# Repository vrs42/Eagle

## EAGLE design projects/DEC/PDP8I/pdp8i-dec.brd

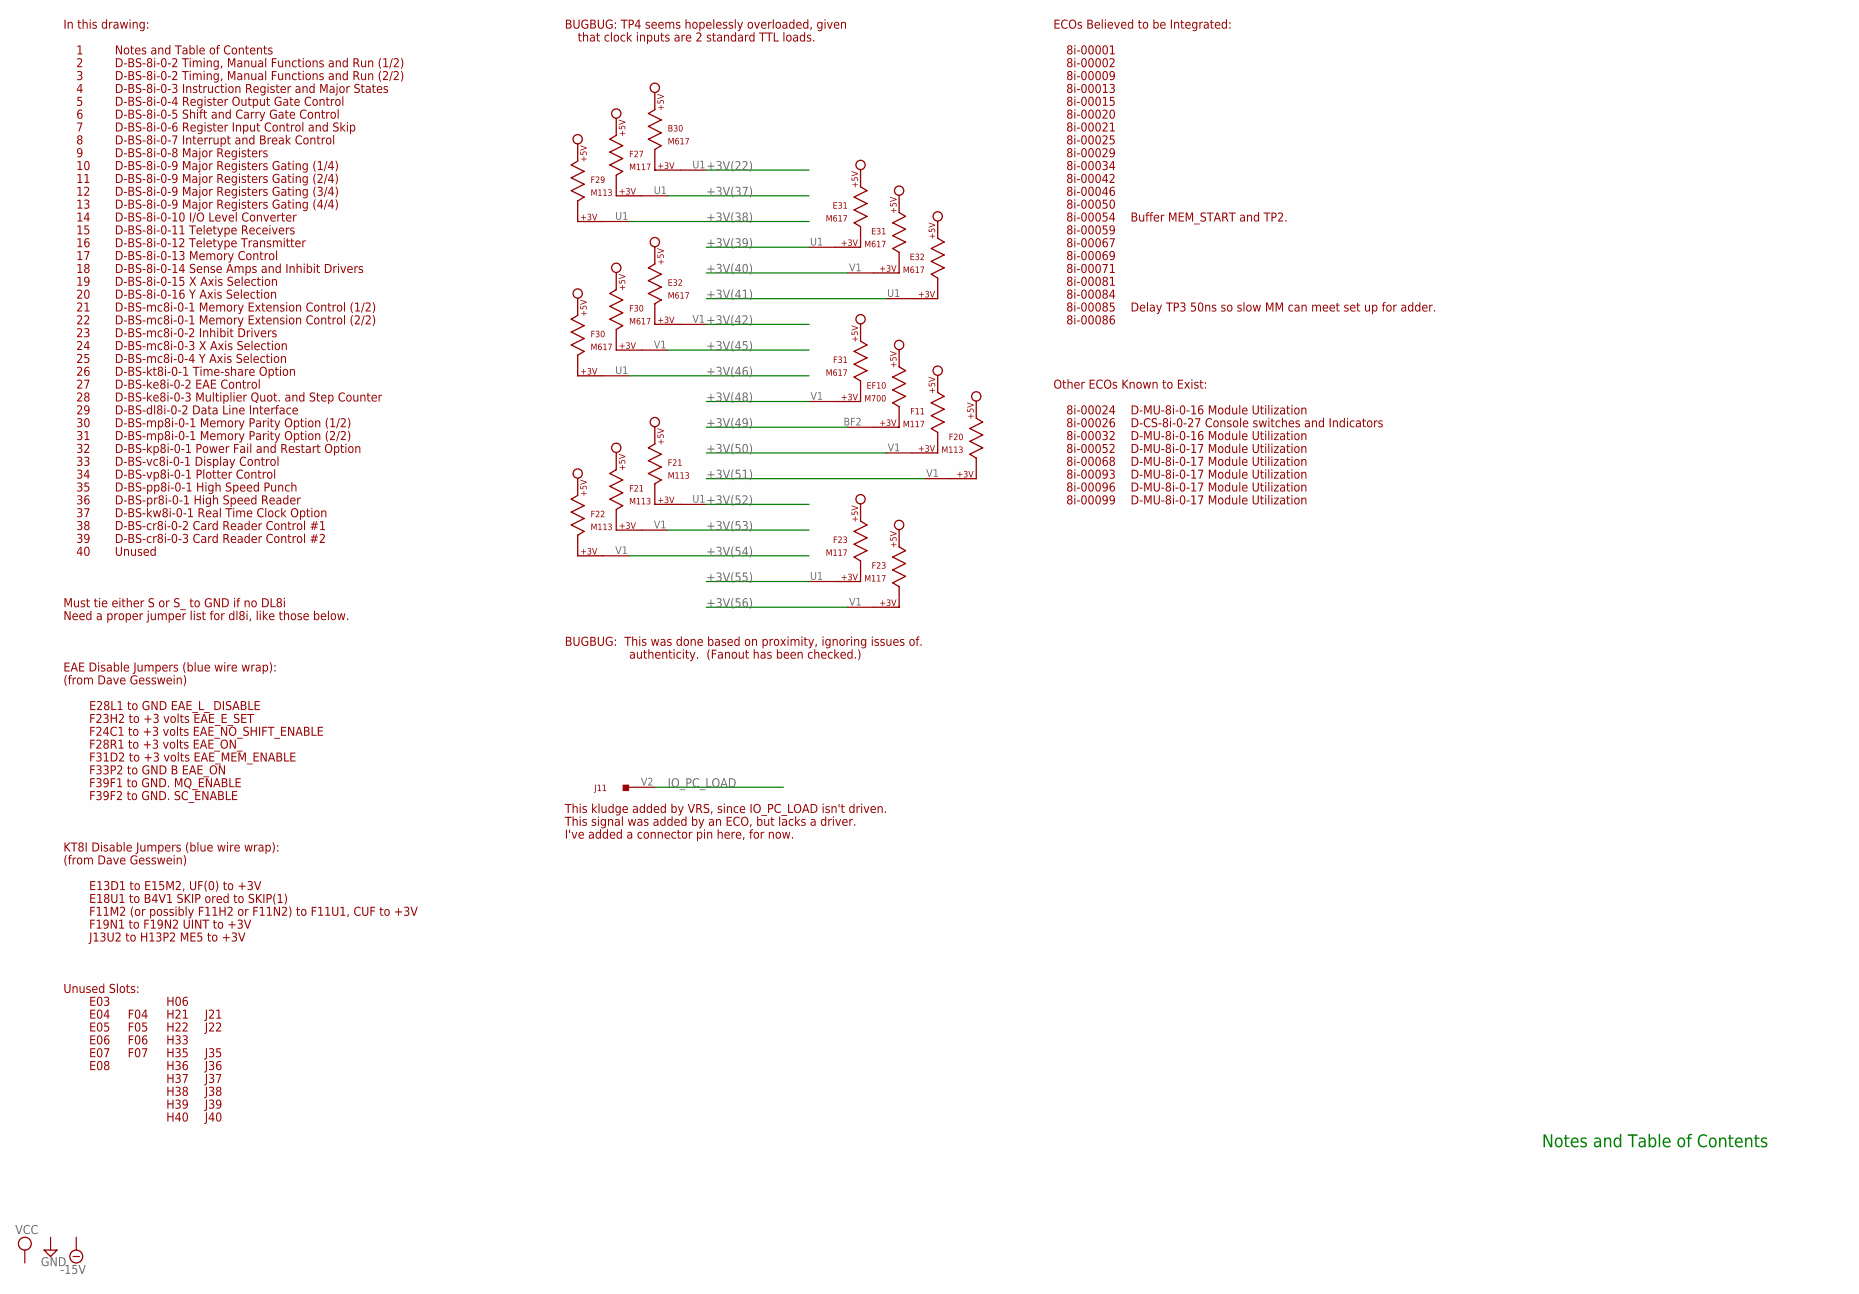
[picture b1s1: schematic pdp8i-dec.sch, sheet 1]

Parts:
B30: M617; H807
E03, E04, E05, E06, E07, E08: EMPTY; H807
E31, E32: M617; H807
EF10: M700; H807-2
F04, F05, F06, F07: EMPTY; H807
F11, F23, F27: M117; H807
F20, F21, F22, F29: M113; H807
F30, F31: M617; H807
H06, H21, H22, H33, H35, H36, H37, H38, H39, H40: EMPTY; H807
J11: W011; H807
J21, J22, J35, J36, J37, J38, J39, J40: EMPTY; H807

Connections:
+3V(22): B30.U1; also elsewhere on the board
+3V(37): F27.U1; also elsewhere on the board
+3V(38): F29.U1; also elsewhere on the board
+3V(39): E31.U1; also elsewhere on the board
+3V(40): E31.V1; also elsewhere on the board
+3V(41): E32.U1; also elsewhere on the board
+3V(42): E32.V1; also elsewhere on the board
+3V(45): F30.V1; also elsewhere on the board
+3V(46): F30.U1; also elsewhere on the board
+3V(48): F31.V1; also elsewhere on the board
+3V(49): EF10.BF2; also elsewhere on the board
+3V(50): F11.V1; also elsewhere on the board
+3V(51): F20.V1; also elsewhere on the board
+3V(52): F21.U1; also elsewhere on the board
+3V(53): F21.V1; also elsewhere on the board
+3V(54): F22.V1; also elsewhere on the board
+3V(55): F23.U1; also elsewhere on the board
+3V(56): F23.V1; also elsewhere on the board
-15V: E03.B2 (-15V), E04.B2 (-15V), E05.B2 (-15V), E06.B2 (-15V), E07.B2 (-15V), E08.B2 (-15V), F04.B2 (-15V), F05.B2 (-15V), F06.B2 (-15V), F07.B2 (-15V), H06.B2 (-15V), H21.B2 (-15V), H22.B2 (-15V), H33.B2 (-15V), H35.B2 (-15V), H36.B2 (-15V), H37.B2 (-15V), H38.B2 (-15V), H39.B2 (-15V), H40.B2 (-15V), J21.B2 (-15V), J22.B2 (-15V), J35.B2 (-15V), J36.B2 (-15V), J37.B2 (-15V), J38.B2 (-15V), J39.B2 (-15V), J40.B2 (-15V); also elsewhere on the board
GND: B30.C2 (GND), B30.T1 (GND), E03.C2 (GND), E04.C2 (GND), E05.C2 (GND), E06.C2 (GND), E07.C2 (GND), E08.C2 (GND), E31.C2 (GND), E31.T1 (GND), E32.C2 (GND), E32.T1 (GND), EF10.AC2 (GND), EF10.BC2 (GND), F04.C2 (GND), F05.C2 (GND), F06.C2 (GND), F07.C2 (GND), F11.C2 (GND), F11.T1 (GND), F20.C2 (GND), F20.T1 (GND), F21.C2 (GND), F21.T1 (GND), F22.C2 (GND), F22.T1 (GND), F23.C2 (GND), F23.T1 (GND), F27.C2 (GND), F27.T1 (GND), F29.C2 (GND), F29.T1 (GND), F30.C2 (GND), F30.T1 (GND), F31.C2 (GND), F31.T1 (GND), H06.C2 (GND), H21.C2 (GND), H22.C2 (GND), H33.C2 (GND), H35.C2 (GND), H36.C2 (GND), H37.C2 (GND), H38.C2 (GND), H39.C2 (GND), H40.C2 (GND), J11.C2 (GND), J11.F2 (GND), J11.J2 (GND), J11.L2 (GND), J11.N2 (GND), J11.R2 (GND), J11.U2 (GND), J21.C2 (GND), J22.C2 (GND), J35.C2 (GND), J36.C2 (GND), J37.C2 (GND), J38.C2 (GND), J39.C2 (GND), J40.C2 (GND); also elsewhere on the board
IO_PC_LOAD: J11.V2; also elsewhere on the board
VCC: B30.A2 (VCC), E03.A2 (VCC), E04.A2 (VCC), E05.A2 (VCC), E06.A2 (VCC), E07.A2 (VCC), E08.A2 (VCC), E31.A2 (VCC), E32.A2 (VCC), EF10.AA2 (VCC), EF10.BA2 (VCC), F04.A2 (VCC), F05.A2 (VCC), F06.A2 (VCC), F07.A2 (VCC), F11.A2 (VCC), F20.A2 (VCC), F21.A2 (VCC), F22.A2 (VCC), F23.A2 (VCC), F27.A2 (VCC), F29.A2 (VCC), F30.A2 (VCC), F31.A2 (VCC), H06.A2 (VCC), H21.A2 (VCC), H22.A2 (VCC), H33.A2 (VCC), H35.A2 (VCC), H36.A2 (VCC), H37.A2 (VCC), H38.A2 (VCC), H39.A2 (VCC), H40.A2 (VCC), J21.A2 (VCC), J22.A2 (VCC), J35.A2 (VCC), J36.A2 (VCC), J37.A2 (VCC), J38.A2 (VCC), J39.A2 (VCC), J40.A2 (VCC); also elsewhere on the board

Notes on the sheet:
BUGBUG: This was done based on proximity, ignoring issues of.
authenticity. (Fanout has been checked.)
EAE Disable Jumpers (blue wire wrap):
F39F1 to GND. MQ_ENABLE
F39F2 to GND. SC_ENABLE
F24C1 to +3 volts EAE_NO_SHIFT_ENABLE
F31D2 to +3 volts EAE_MEM_ENABLE
F33P2 to GND B EAE_ON
F28R1 to +3 volts EAE_ON_
F23H2 to +3 volts EAE_E_SET
E28L1 to GND EAE_L_ DISABLE
Must tie either S or S_ to GND if no DL8i
F11M2 (or possibly F11H2 or F11N2) to F11U1, CUF to +3V
E13D1 to E15M2, UF(0) to +3V
J13U2 to H13P2 ME5 to +3V
F19N1 to F19N2 UINT to +3V
E18U1 to B4V1 SKIP ored to SKIP(1)
KT8I Disable Jumpers (blue wire wrap):
(from Dave Gesswein)
In this drawing:
Unused Slots:
Notes and Table of Contents
ECOs Believed to be Integrated:
8i-00001
8i-00085
Buffer MEM_START and TP2.
Delay TP3 50ns so slow MM can meet set up for adder.
Need a proper jumper list for dl8i, like those below.
This signal was added by an ECO, but lacks a driver.
I've added a connector pin here, for now.
BUGBUG: TP4 seems hopelessly overloaded, given
8i-00013
8i-00054
8i-00002
8i-00015
8i-00020
8i-00021
8i-00025
8i-00050
8i-00042

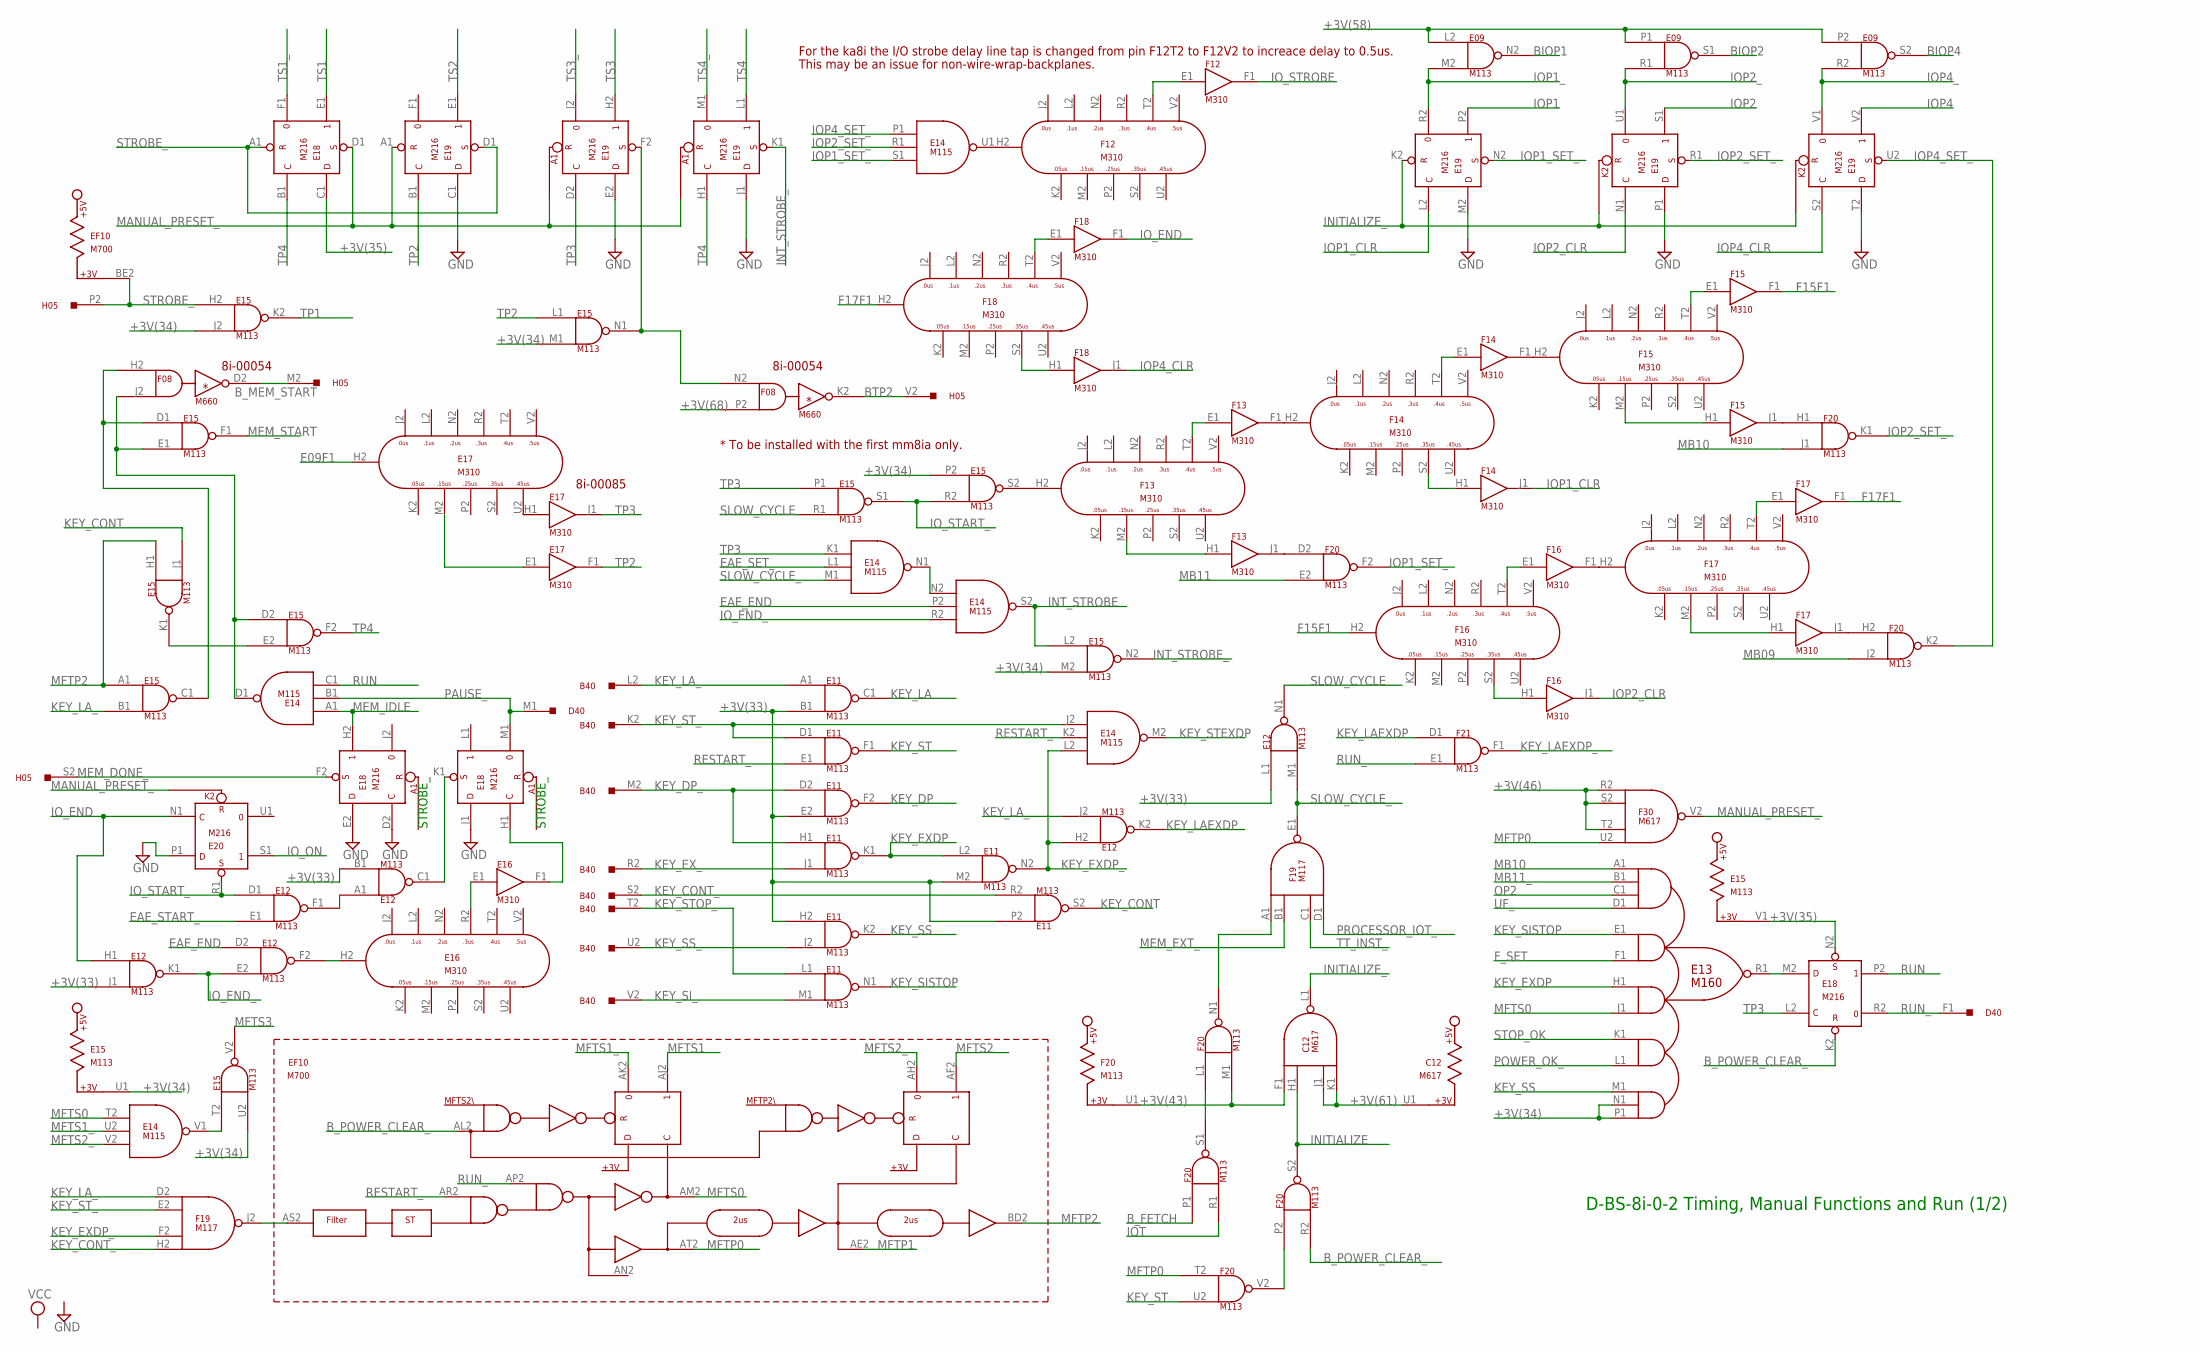
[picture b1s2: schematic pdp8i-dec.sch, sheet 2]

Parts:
B40: W077; H807
C12: M617; H807
D40: M900; H807
E09, E11, E12, E15: M113; H807
E13: M160; H807
E14: M115; H807
E16, E17: M310; H807
E18, E19, E20: M216; H807
EF10: M700; H807-2
F08: M660; H807
F12, F13, F14, F15, F16, F17, F18: M310; H807
F19: M117; H807
F20, F21: M113; H807
F30: M617; H807
H05: W011; H807

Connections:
+3V(33): E11.B1 (IN2), E11.E2 (IN2), E11.H2 (IN1), E11.M2 (IN2), E11.P2 (IN1), E12.B1 (IN2), E12.J1 (IN2), E12.L1 (IN1); also elsewhere on the board
+3V(34): E13.N1 (IN5B), E13.P1 (IN5C), E15.J2 (IN2), E15.M1 (IN2), E15.M2 (IN2), E15.P2 (IN1), E15.U1, E15.U2 (IN2)
+3V(35): E15.V1, E18.C1 (D), E18.N2 (S); also elsewhere on the board
+3V(43): C12.F1 (IN1), F20.M1 (IN2), F20.U1; also elsewhere on the board
+3V(46): F30.R2 (IN1), F30.S2 (IN2), F30.T2 (IN3); also elsewhere on the board
+3V(58): E09.L2 (IN1), E09.P1 (IN1), E09.P2 (IN1); also elsewhere on the board
+3V(61): C12.J1 (IN3), C12.K1 (IN4), C12.U1; also elsewhere on the board
+3V(68): F08.P2 (IN2); also elsewhere on the board
BIOP1: E09.N2 (OUT); also elsewhere on the board
BIOP2: E09.S1 (OUT); also elsewhere on the board
BIOP4: E09.S2 (OUT); also elsewhere on the board
BTP2: F08.K2 (OUT), H05.V2
B_FETCH: F20.P1 (IN1); also elsewhere on the board
B_MEM_START: F08.D2 (OUT), H05.M2
B_POWER_CLEAR_: E18.K2 (R), EF10.AL2 (CL2), F20.R2 (IN2); also elsewhere on the board
E09F1: E17.H2; also elsewhere on the board
EAE_END: E12.D2 (IN1), E14.P2 (IN2); also elsewhere on the board
EAE_SET_: E14.L1 (IN2); also elsewhere on the board
EAE_START_: E12.E1 (IN2); also elsewhere on the board
F15F1: F15.F1 (OUT), F16.H2
F17F1: F17.F1 (OUT), F18.H2
F_SET: E13.F1 (IN2B); also elsewhere on the board
GND: C12.C2 (GND), C12.T1 (GND), E09.C2 (GND), E09.T1 (GND), E11.C2 (GND), E11.T1 (GND), E12.C2 (GND), E12.T1 (GND), E13.C2 (GND), E13.T1 (GND), E14.C2 (GND), E14.T1 (GND), E15.C2 (GND), E15.T1 (GND), E16.C2 (GND), E16.T1 (GND), E17.C2 (GND), E17.T1 (GND), E18.C2 (GND), E18.D2 (C), E18.E2 (D), E18.J1 (D), E18.T1 (GND), E19.C1 (D), E19.C2 (GND), E19.E2 (D), E19.J1 (D), E19.M2 (D), E19.P1 (D), E19.T1 (GND), E19.T2 (D), E20.C2 (GND), E20.P1 (D), E20.T1 (GND), EF10.AC2 (GND), EF10.BC2 (GND), F08.C2 (GND), F12.C2 (GND), F12.T1 (GND), F13.C2 (GND), F13.T1 (GND), F14.C2 (GND), F14.T1 (GND), F15.C2 (GND), F15.T1 (GND), F16.C2 (GND), F16.T1 (GND), F17.C2 (GND), F17.T1 (GND), F18.C2 (GND), F18.T1 (GND), F19.C2 (GND), F19.T1 (GND), F20.C2 (GND), F20.T1 (GND), F21.C2 (GND), F21.T1 (GND), F30.C2 (GND), F30.T1 (GND), H05.C2 (GND), H05.F2 (GND), H05.J2 (GND), H05.L2 (GND), H05.N2 (GND), H05.R2 (GND), H05.U2 (GND); also elsewhere on the board
INITIALIZE: C12.H1 (IN2), F20.S2 (OUT); also elsewhere on the board
INITIALIZE_: C12.L1 (OUT), E19.K2 (R); also elsewhere on the board
INT_STROBE: E14.S2 (OUT), E15.L2 (IN1); also elsewhere on the board
INT_STROBE_: E15.N2 (OUT), E19.K1 (S); also elsewhere on the board
IOP1: E19.P2 (1); also elsewhere on the board
IOP1_: E09.M2 (IN2), E19.R2 (0); also elsewhere on the board
IOP1_CLR: E19.L2 (C), F14.J1 (OUT)
IOP1_SET_: E14.S1 (IN3), E19.N2 (S), F20.F2 (OUT)
IOP2: E19.S1 (1); also elsewhere on the board
IOP2_: E09.R1 (IN2), E19.U1 (0); also elsewhere on the board
IOP2_CLR: E19.N1 (C), F16.J1 (OUT)
IOP2_SET_: E14.R1 (IN2), E19.R1 (S), F20.K1 (OUT)
IOP4: E19.V2 (1); also elsewhere on the board
IOP4_: E09.R2 (IN2), E19.V1 (0); also elsewhere on the board
IOP4_CLR: E19.S2 (C), F18.J1 (OUT)
IOP4_SET_: E14.P1 (IN1), E19.U2 (S), F20.K2 (OUT)
IOT: F20.R1 (IN2); also elsewhere on the board
IO_END: E12.H1 (IN1), E20.N1 (C), F18.F1 (OUT)
IO_END_: E12.E2 (IN2), E12.K1 (OUT), E14.R2 (IN3)
IO_ON: E20.S1 (1); also elsewhere on the board
IO_START_: E12.D1 (IN1), E15.R2 (IN2), E15.S1 (OUT), E20.R1 (S)
IO_STROBE: F12.F1 (OUT); also elsewhere on the board
KEY_CONT: E11.S2 (OUT), E15.J1 (IN2)
KEY_CONT_: B40.S2, E11.R2 (IN2), F19.H2 (IN4)
KEY_DP: E11.F2 (OUT); also elsewhere on the board
KEY_DP_: B40.M2, E11.D2 (IN1), E11.H1 (IN1)
KEY_EXDP: E11.K1 (OUT), E11.L2 (IN1), E13.H1 (IN3A); also elsewhere on the board
KEY_EXDP_: E11.N2 (OUT), E12.H2 (IN1), E14.L2 (IN3), F19.F2 (IN3)
KEY_EX_: B40.R2, E11.J1 (IN2)
KEY_LA: E11.C1 (OUT); also elsewhere on the board
KEY_LAEXDP: E12.K2 (OUT), F21.D1 (IN1); also elsewhere on the board
KEY_LAEXDP_: F21.F1 (OUT); also elsewhere on the board
KEY_LA_: B40.L2, E11.A1 (IN1), E12.J2 (IN2), E15.B1 (IN2), F19.D2 (IN1)
KEY_SISTOP: E11.N1 (OUT), E13.E1 (IN2A)
KEY_SI_: B40.V2, E11.M1 (IN2)
KEY_SS: E11.K2 (OUT), E13.M1 (IN5A)
KEY_SS_: B40.U2, E11.J2 (IN2)
KEY_ST: E11.F1 (OUT), F20.U2 (IN2); also elsewhere on the board
KEY_STEXDP: E14.M2 (OUT); also elsewhere on the board
KEY_STOP_: B40.T2, E11.L1 (IN1)
KEY_ST_: B40.K2, E11.D1 (IN1), E14.J2 (IN1), F19.E2 (IN2)
MANUAL_PRESET_: E18.D1 (S), E19.A1 (R), F30.V2 (OUT); also elsewhere on the board
MB09: F20.J2 (IN2); also elsewhere on the board
MB10: E13.A1 (IN1A), F20.J1 (IN2); also elsewhere on the board
MB11: F20.E2 (IN2); also elsewhere on the board
MB11_: E13.B1 (IN1B); also elsewhere on the board
MEM_DONE_: E18.F2 (S), H05.S2; also elsewhere on the board
MEM_EXT_: F19.B1 (IN2); also elsewhere on the board
MEM_IDLE: E14.A1 (IN1), E18.H2 (1)
MEM_START: E15.F1 (OUT); also elsewhere on the board
MFTP0: EF10.AT2 (CT2), F20.T2 (IN1), F30.U2 (IN4)
MFTP1: EF10.AE2 (CE2); also elsewhere on the board
MFTP2: E15.A1 (IN1), E15.H1 (IN1), EF10.BD2 (DD2); also elsewhere on the board
MFTS0: E13.J1 (IN3B), E14.T2 (IN1), EF10.AM2 (CM2); also elsewhere on the board
MFTS1: EF10.AJ2 (CJ2); also elsewhere on the board
MFTS1_: E14.U2 (IN2), EF10.AK2 (CK2)
MFTS2: EF10.AF2 (CF2); also elsewhere on the board
MFTS2_: E14.V2 (IN3), EF10.AH2 (CH2); also elsewhere on the board
MFTS3: E15.V2 (OUT); also elsewhere on the board
unnamed: EF10.AS2 (CS2), F19.J2 (OUT)
unnamed: F20.P2 (IN1), F20.V2 (OUT)
unnamed: F20.L1 (IN1), F20.S1 (OUT)
unnamed: E13.R1 (OUT), E18.M2 (D)
unnamed: F19.A1 (IN1), F20.N1 (OUT)
unnamed: E14.V1 (OUT), E15.T2 (IN1)
unnamed: E16.E1 (IN), E16.R2
unnamed: E12.A1 (IN1), E12.F1 (OUT)
unnamed: E12.C1 (OUT), E18.K1 (S)
unnamed: E12.F2 (OUT), E16.H2
unnamed: E16.F1 (OUT), E18.H1 (C)
unnamed: E14.D1 (OUT), E15.D2 (IN1), E15.E1 (IN2), F08.J2 (IN2)
unnamed: E15.C1 (OUT), E15.D1 (IN1), F08.H2 (IN1)
unnamed: E15.E2 (IN2), E15.K1 (OUT)
unnamed: E17.E1 (IN), E17.M2
unnamed: E15.N1 (OUT), E19.F2 (S), F08.N2 (IN1)
unnamed: E14.N1 (OUT), E14.N2 (IN1)
unnamed: E15.S2 (OUT), F13.H2
unnamed: F13.H1 (IN), F13.M2
unnamed: F13.E1 (IN), F13.T2
unnamed: F13.F1 (OUT), F14.H2
unnamed: F14.H1 (IN), F14.S2
unnamed: F14.E1 (IN), F14.T2
unnamed: F14.F1 (OUT), F15.H2
unnamed: F13.J1 (OUT), F20.D2 (IN1)
unnamed: F15.H1 (IN), F15.M2
unnamed: F15.E1 (IN), F15.T2
unnamed: F15.J1 (OUT), F20.H1 (IN1)
unnamed: F16.H1 (IN), F16.S2
unnamed: F16.E1 (IN), F16.T2
unnamed: F16.F1 (OUT), F17.H2
unnamed: F17.H1 (IN), F17.M2
unnamed: F17.E1 (IN), F17.T2
unnamed: F17.J1 (OUT), F20.H2 (IN1)
unnamed: E14.U1 (OUT), F12.H2
unnamed: F12.E1 (IN), F12.T2
unnamed: F18.H1 (IN), F18.S2
unnamed: F18.E1 (IN), F18.T2
unnamed: E17.H1 (IN), E17.U2
OP2: E13.C1 (IN1C); also elsewhere on the board
PAUSE_: D40.M1, E14.B1 (IN2), E18.M1 (0)
POWER_OK_: E13.L1 (IN4B); also elsewhere on the board
PROCESSOR_IOT_: F19.D1 (IN4); also elsewhere on the board
RESTART_: E11.E1 (IN2), E14.K2 (IN2), EF10.AR2 (CR2); also elsewhere on the board
RUN: E14.C1 (IN3), E18.P2 (1); also elsewhere on the board
RUN_: D40.F1, E18.R2 (0), EF10.AP2 (CP2), F21.E1 (IN2); also elsewhere on the board
SLOW_CYCLE: E12.N1 (OUT), E15.R1 (IN2)
SLOW_CYCLE_: E12.M1 (IN2), E14.M1 (IN3), F19.E1 (OUT)
STOP_OK: E13.K1 (IN4A); also elsewhere on the board
STROBE_: E15.H2 (IN1), E18.A1 (R), E19.D1 (S), EF10.BE2, H05.P2; also elsewhere on the board
TP1: E15.K2 (OUT); also elsewhere on the board
TP2: E15.L1 (IN1), E17.F1 (OUT), E19.B1 (C); also elsewhere on the board
TP3: E14.K1 (IN1), E15.P1 (IN1), E17.J1 (OUT), E18.L2 (C), E19.D2 (C); also elsewhere on the board
TP4: E15.F2 (OUT), E18.B1 (C), E19.H1 (C); also elsewhere on the board
TS1: E18.E1 (1); also elsewhere on the board
TS1_: E18.F1 (0); also elsewhere on the board
TS2: E19.E1 (1); also elsewhere on the board
TS3: E19.H2 (1); also elsewhere on the board
TS3_: E19.J2 (0); also elsewhere on the board
TS4: E19.L1 (1); also elsewhere on the board
TS4_: E19.M1 (0); also elsewhere on the board
TT_INST_: F19.C1 (IN3); also elsewhere on the board
UF_: E13.D1 (IN1D); also elsewhere on the board
VCC: C12.A2 (VCC), E09.A2 (VCC), E11.A2 (VCC), E12.A2 (VCC), E13.A2 (VCC), E14.A2 (VCC), E15.A2 (VCC), E16.A2 (VCC), E17.A2 (VCC), E18.A2 (VCC), E19.A2 (VCC), E20.A2 (VCC), EF10.AA2 (VCC), EF10.BA2 (VCC), F08.A2 (VCC), F12.A2 (VCC), F13.A2 (VCC), F14.A2 (VCC), F15.A2 (VCC), F16.A2 (VCC), F17.A2 (VCC), F18.A2 (VCC), F19.A2 (VCC), F20.A2 (VCC), F21.A2 (VCC), F30.A2 (VCC); also elsewhere on the board

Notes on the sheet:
D-BS-8i-0-2 Timing, Manual Functions and Run (1/2)
STROBE_
8i-00085
8i-00054
For the ka8i the I/O strobe delay line tap is changed from pin F12T2 to F12V2 to increace delay to 0.5us.
* To be installed with the first mm8ia only.
This may be an issue for non-wire-wrap-backplanes.

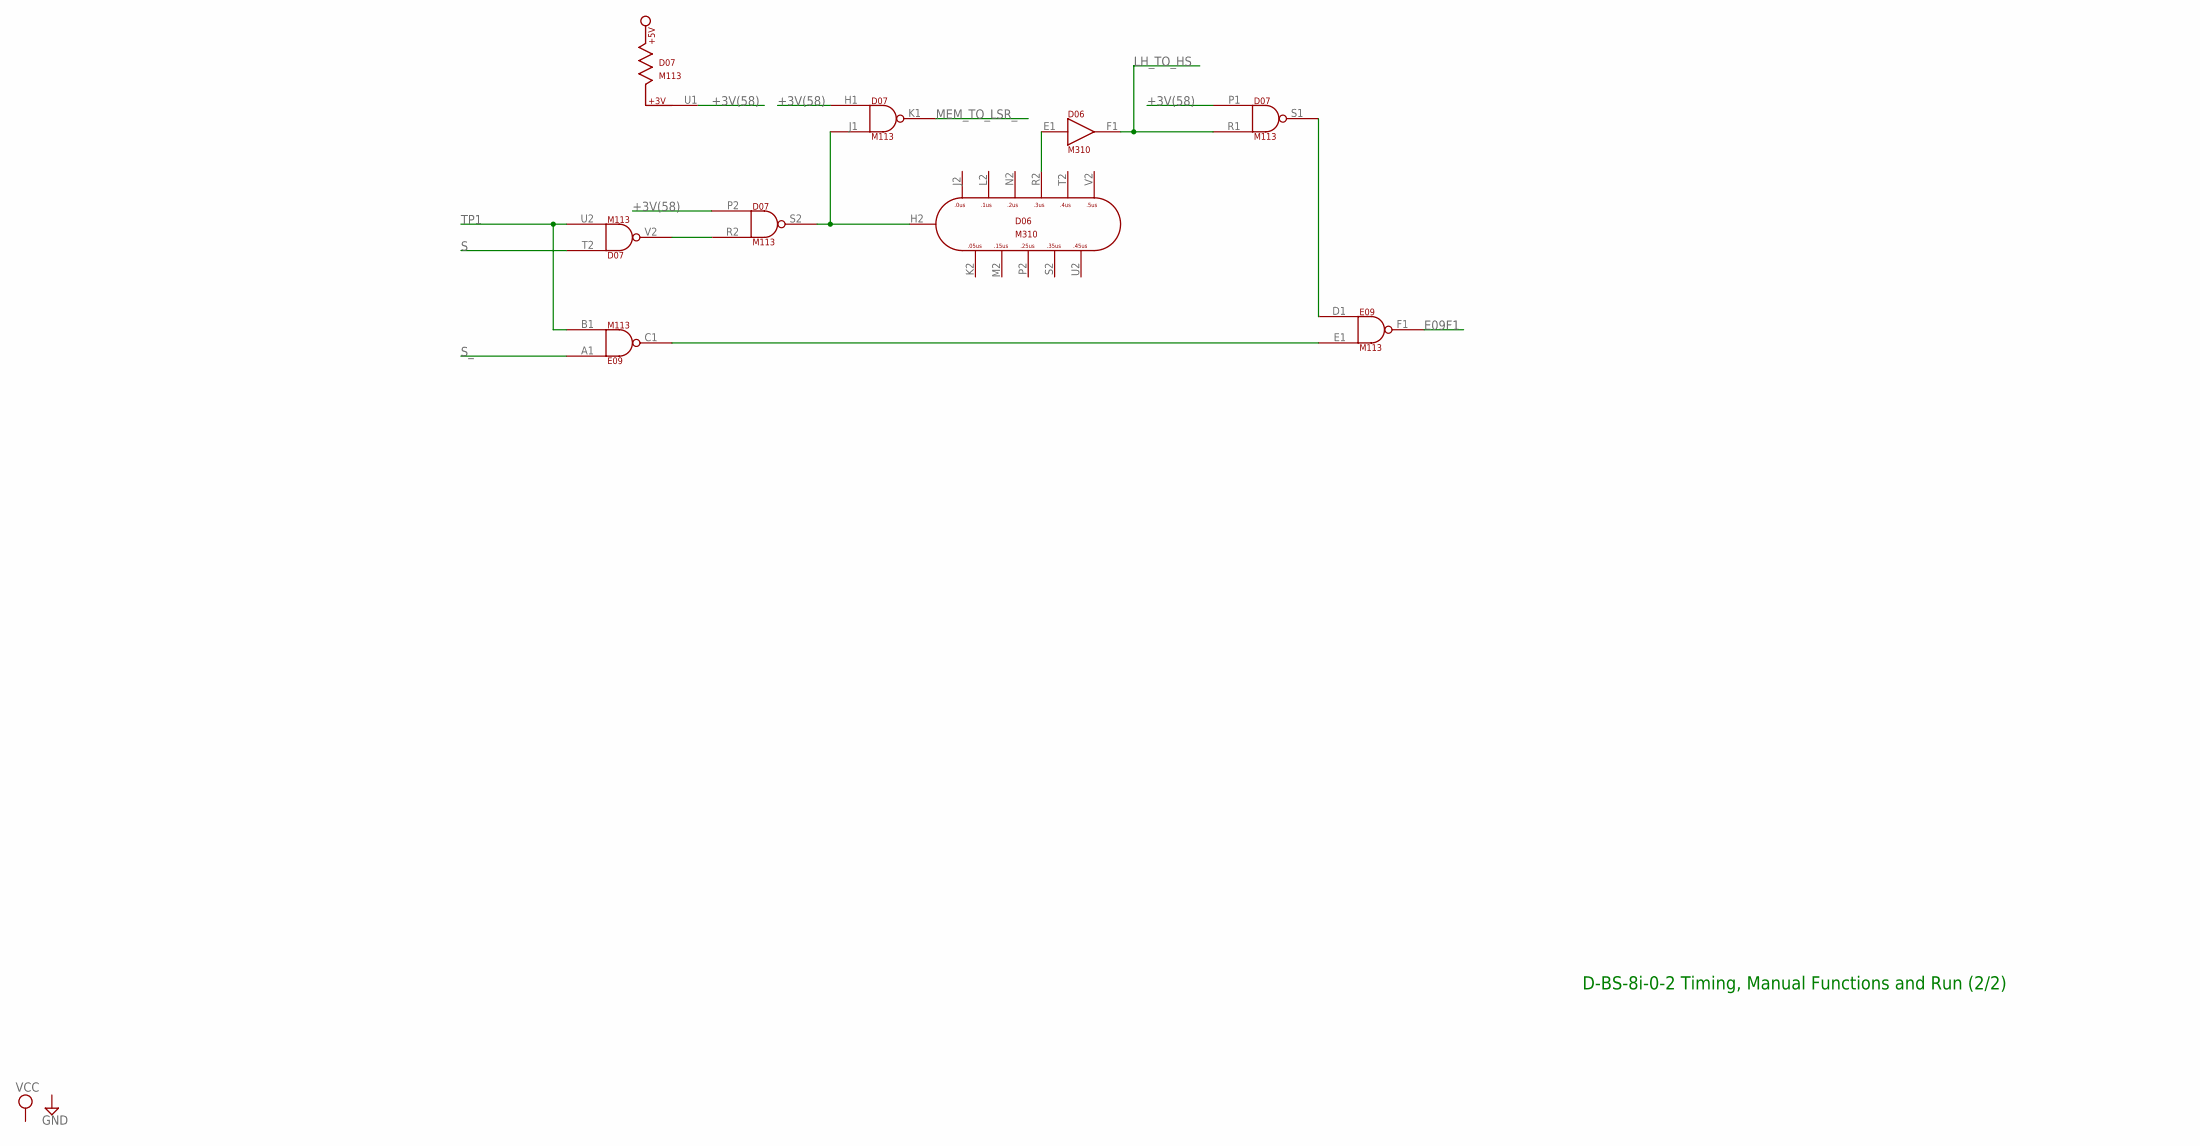
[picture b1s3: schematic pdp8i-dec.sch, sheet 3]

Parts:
D06: M310; H807
D07: M113; H807
E09: M113; H807

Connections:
+3V(58): D07.H1 (IN1), D07.P1 (IN1), D07.P2 (IN1), D07.U1; also elsewhere on the board
E09F1: E09.F1 (OUT); also elsewhere on the board
GND: D06.C2 (GND), D06.T1 (GND), D07.C2 (GND), D07.T1 (GND), E09.C2 (GND), E09.T1 (GND); also elsewhere on the board
LH_TO_HS: D06.F1 (OUT), D07.R1 (IN2); also elsewhere on the board
MEM_TO_LSR_: D07.K1 (OUT); also elsewhere on the board
unnamed: E09.C1 (OUT), E09.E1 (IN2)
unnamed: D07.R2 (IN2), D07.V2 (OUT)
unnamed: D06.H2, D07.J1 (IN2), D07.S2 (OUT)
unnamed: D06.E1 (IN), D06.R2
unnamed: D07.S1 (OUT), E09.D1 (IN1)
S: D07.T2 (IN1); also elsewhere on the board
S_: E09.A1 (IN1); also elsewhere on the board
TP1: D07.U2 (IN2), E09.B1 (IN2); also elsewhere on the board
VCC: D06.A2 (VCC), D07.A2 (VCC), E09.A2 (VCC); also elsewhere on the board

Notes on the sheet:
D-BS-8i-0-2 Timing, Manual Functions and Run (2/2)

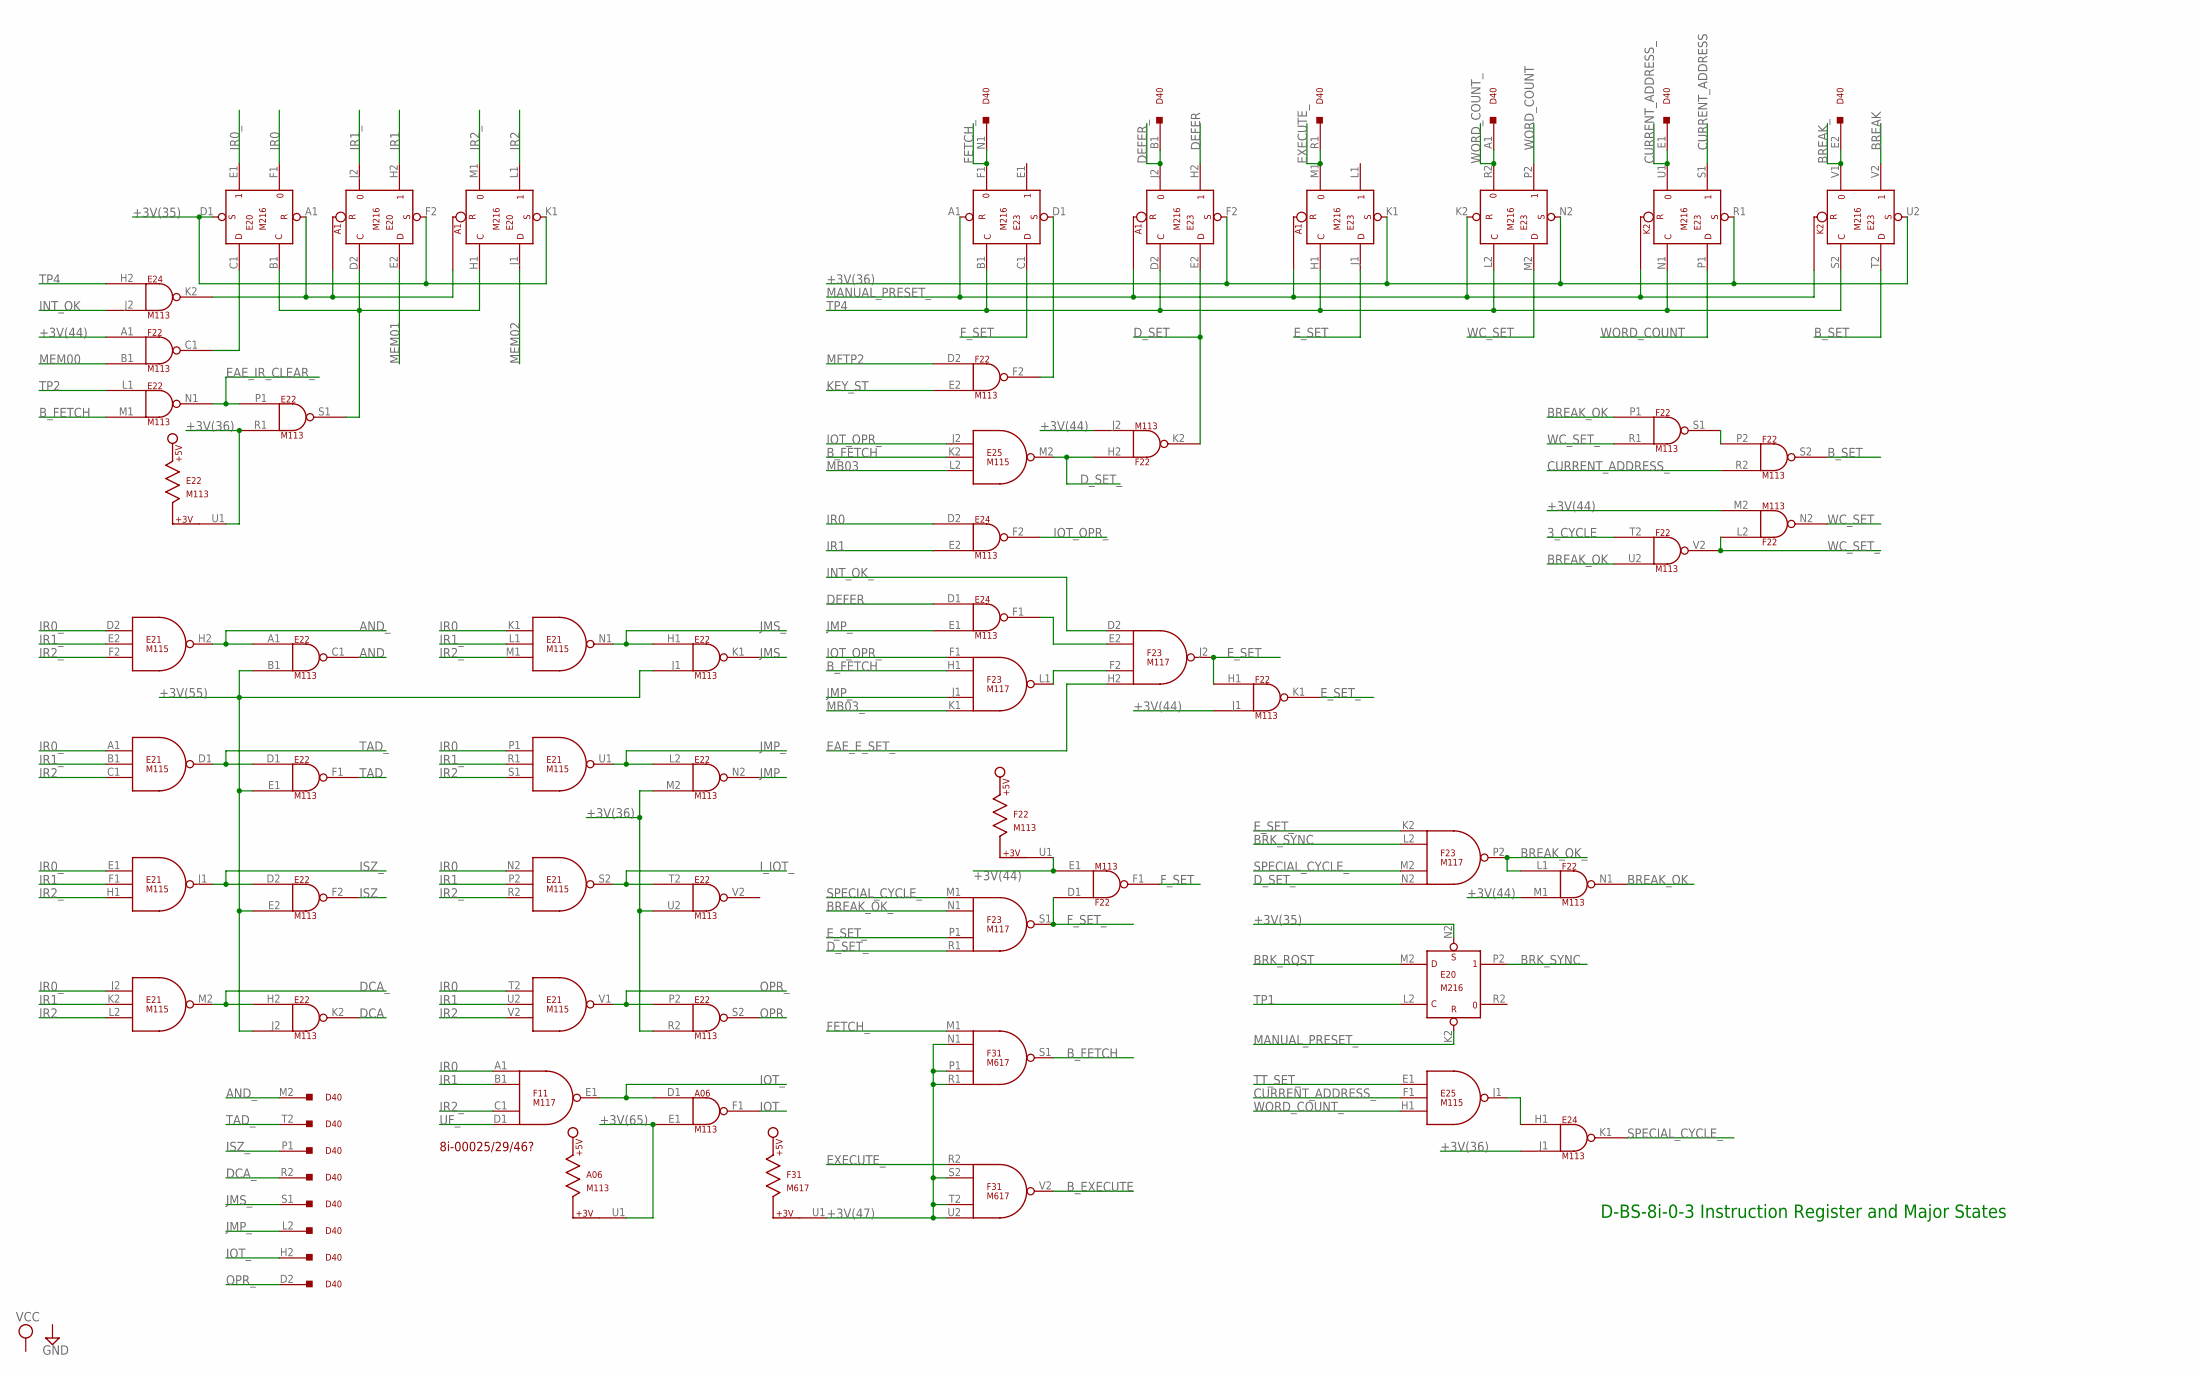
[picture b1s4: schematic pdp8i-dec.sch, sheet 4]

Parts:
A06: M113; H807
D40: M900; H807
E20, E23: M216; H807
E21, E25: M115; H807
E22, E24: M113; H807
F11, F23: M117; H807
F22: M113; H807
F31: M617; H807

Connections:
3_CYCLE: F22.T2 (IN1); also elsewhere on the board
+3V(35): E20.D1 (S), E20.F2 (S), E20.K1 (S), E20.N2 (S); also elsewhere on the board
+3V(36): E22.M2 (IN2), E22.R1 (IN2), E22.R2 (IN2), E22.U1, E22.U2 (IN2), E23.F2 (S), E23.K1 (S), E23.N2 (S), E23.R1 (S), E23.U2 (S), E24.J1 (IN2); also elsewhere on the board
+3V(44): F22.A1 (IN1), F22.E1 (IN2), F22.J1 (IN2), F22.J2 (IN2), F22.M1 (IN2), F22.M2 (IN2), F22.U1; also elsewhere on the board
+3V(47): F31.N1 (IN2), F31.P1 (IN3), F31.R1 (IN4), F31.S2 (IN2), F31.T2 (IN3), F31.U1, F31.U2 (IN4); also elsewhere on the board
+3V(55): E22.B1 (IN2), E22.E1 (IN2), E22.E2 (IN2), E22.J1 (IN2), E22.J2 (IN2); also elsewhere on the board
+3V(65): A06.E1 (IN2), A06.U1; also elsewhere on the board
AND: E22.C1 (OUT); also elsewhere on the board
AND_: D40.M2, E21.H2 (OUT), E22.A1 (IN1); also elsewhere on the board
BREAK: E23.V2 (1); also elsewhere on the board
BREAK_: D40.E2, E23.V1 (0); also elsewhere on the board
BREAK_OK: F22.N1 (OUT), F22.P1 (IN1), F22.U2 (IN2); also elsewhere on the board
BREAK_OK_: F22.L1 (IN1), F23.N1 (IN2), F23.P2 (OUT); also elsewhere on the board
BRK_RQST: E20.M2 (D); also elsewhere on the board
BRK_SYNC: E20.P2 (1), F23.L2 (IN2)
B_EXECUTE: F31.V2 (OUT); also elsewhere on the board
B_FETCH: E22.M1 (IN2), E25.K2 (IN2), F23.H1 (IN2), F31.S1 (OUT); also elsewhere on the board
B_SET: E23.T2 (D), F22.S2 (OUT); also elsewhere on the board
CURRENT_ADDRESS: E23.S1 (1); also elsewhere on the board
CURRENT_ADDRESS_: D40.E1, E23.U1 (0), E25.F1 (IN2), F22.R2 (IN2)
DCA: E22.K2 (OUT); also elsewhere on the board
DCA_: D40.R2, E21.M2 (OUT), E22.H2 (IN1); also elsewhere on the board
DEFER: E23.H2 (1), E24.D1 (IN1); also elsewhere on the board
DEFER_: D40.B1, E23.J2 (0)
D_SET: E23.E2 (D), F22.K2 (OUT)
D_SET_: E25.M2 (OUT), F22.H2 (IN1), F23.N2 (IN4), F23.R1 (IN4); also elsewhere on the board
EAE_E_SET_: F23.H2 (IN4); also elsewhere on the board
EAE_IR_CLEAR_: E22.N1 (OUT), E22.P1 (IN1); also elsewhere on the board
EXECUTE_: D40.R1, E23.M1 (0), F31.R2 (IN1)
E_SET: E23.J1 (D), F22.H1 (IN1), F23.J2 (OUT)
E_SET_: F22.K1 (OUT), F23.K2 (IN1), F23.P1 (IN3); also elsewhere on the board
FETCH_: D40.N1, E23.F1 (0), F31.M1 (IN1); also elsewhere on the board
F_SET: E23.C1 (D), F22.F1 (OUT); also elsewhere on the board
F_SET_: F22.D1 (IN1), F23.S1 (OUT); also elsewhere on the board
GND: A06.C2 (GND), A06.T1 (GND), E20.C2 (GND), E20.T1 (GND), E21.C2 (GND), E21.T1 (GND), E22.C2 (GND), E22.T1 (GND), E23.C2 (GND), E23.T1 (GND), E24.C2 (GND), E24.T1 (GND), E25.C2 (GND), E25.T1 (GND), F11.C2 (GND), F11.T1 (GND), F22.C2 (GND), F22.T1 (GND), F23.C2 (GND), F23.T1 (GND), F31.C2 (GND), F31.T1 (GND); also elsewhere on the board
INT_OK: E24.J2 (IN2); also elsewhere on the board
INT_OK_: F23.D2 (IN1); also elsewhere on the board
IOT: A06.F1 (OUT); also elsewhere on the board
IOT_: A06.D1 (IN1), D40.H2, F11.E1 (OUT)
IOT_OPR_: E24.F2 (OUT), E25.J2 (IN1), F23.F1 (IN1)
IR0: E20.F1 (0), E21.K1 (IN1), E21.N2 (IN1), E21.P1 (IN1), E21.T2 (IN1), E24.D2 (IN1), F11.A1 (IN1)
IR0_: E20.E1 (1), E21.A1 (IN1), E21.D2 (IN1), E21.E1 (IN1), E21.J2 (IN1)
IR1: E20.H2 (1), E21.F1 (IN2), E21.K2 (IN2), E21.P2 (IN2), E21.U2 (IN2), E24.E2 (IN2), F11.B1 (IN2)
IR1_: E20.J2 (0), E21.B1 (IN2), E21.E2 (IN2), E21.L1 (IN2), E21.R1 (IN2)
IR2: E20.L1 (1), E21.C1 (IN3), E21.L2 (IN3), E21.S1 (IN3), E21.V2 (IN3)
IR2_: E20.M1 (0), E21.F2 (IN3), E21.H1 (IN3), E21.M1 (IN3), E21.R2 (IN3), F11.C1 (IN3)
ISZ: E22.F2 (OUT); also elsewhere on the board
ISZ_: D40.P1, E21.J1 (OUT), E22.D2 (IN1)
I_IOT_: E21.S2 (OUT), E22.T2 (IN1); also elsewhere on the board
JMP: E22.N2 (OUT); also elsewhere on the board
JMP_: D40.L2, E21.U1 (OUT), E22.L2 (IN1), E24.E1 (IN2), F23.J1 (IN3); also elsewhere on the board
JMS: E22.K1 (OUT); also elsewhere on the board
JMS_: D40.S1, E21.N1 (OUT), E22.H1 (IN1); also elsewhere on the board
KEY_ST: F22.E2 (IN2); also elsewhere on the board
MANUAL_PRESET_: E20.K2 (R), E23.A1 (R), E23.K2 (R); also elsewhere on the board
MB03: E25.L2 (IN3); also elsewhere on the board
MB03_: F23.K1 (IN4); also elsewhere on the board
MEM00: F22.B1 (IN2); also elsewhere on the board
MEM01: E20.E2 (D); also elsewhere on the board
MEM02: E20.J1 (D); also elsewhere on the board
MFTP2: F22.D2 (IN1); also elsewhere on the board
unnamed: E20.A1 (R), E24.K2 (OUT)
unnamed: E20.C1 (D), F22.C1 (OUT)
unnamed: E20.B1 (C), E20.D2 (C), E20.H1 (C), E22.S1 (OUT)
unnamed: E23.D1 (S), F22.F2 (OUT)
unnamed: E24.F1 (OUT), F23.E2 (IN2)
unnamed: F23.F2 (IN3), F23.L1 (OUT)
unnamed: F22.P2 (IN1), F22.S1 (OUT)
unnamed: E24.H1 (IN1), E25.J1 (OUT)
OPR: E22.S2 (OUT); also elsewhere on the board
OPR_: D40.D2, E21.V1 (OUT), E22.P2 (IN1)
SPECIAL_CYCLE_: E24.K1 (OUT), F23.M1 (IN1), F23.M2 (IN3)
TAD: E22.F1 (OUT); also elsewhere on the board
TAD_: D40.T2, E21.D1 (OUT), E22.D1 (IN1); also elsewhere on the board
TP1: E20.L2 (C); also elsewhere on the board
TP2: E22.L1 (IN1); also elsewhere on the board
TP4: E23.B1 (C), E23.D2 (C), E23.H1 (C), E23.L2 (C), E23.N1 (C), E23.S2 (C), E24.H2 (IN1); also elsewhere on the board
TT_SET_: E25.E1 (IN1); also elsewhere on the board
UF_: F11.D1 (IN4); also elsewhere on the board
VCC: A06.A2 (VCC), E20.A2 (VCC), E21.A2 (VCC), E22.A2 (VCC), E23.A2 (VCC), E24.A2 (VCC), E25.A2 (VCC), F11.A2 (VCC), F22.A2 (VCC), F23.A2 (VCC), F31.A2 (VCC); also elsewhere on the board
WC_SET: E23.M2 (D), F22.N2 (OUT)
WC_SET_: F22.L2 (IN1), F22.R1 (IN2), F22.V2 (OUT); also elsewhere on the board
WORD_COUNT: E23.P1 (D), E23.P2 (1); also elsewhere on the board
WORD_COUNT_: D40.A1, E23.R2 (0), E25.H1 (IN3); also elsewhere on the board

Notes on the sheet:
D-BS-8i-0-3 Instruction Register and Major States
8i-00025/29/46?
